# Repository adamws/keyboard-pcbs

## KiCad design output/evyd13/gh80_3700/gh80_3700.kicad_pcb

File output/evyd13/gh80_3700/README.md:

## evyd13/gh80_3700

[layout](gh80_3700-kle.json) - [PCB](gh80_3700.kicad_pcb)

{:loading="lazy"}

[Open in keyboard-layout-editor](http://www.keyboard-layout-editor.com/##@@_c=#aaaaaa;&=0,0&=0,1&=0,2&=0,3;&@_y:1&c=#777777;&=1,0&_c=#aaaaaa;&=1,1&=1,2&=1,3;&@_c=#cccccc;&=2,0&=2,1&=2,2&_c=#aaaaaa&h:2;&=3,3%0A%0A%0A1,0;&@_c=#cccccc;&=3,0&=3,1&=3,2;&@=4,0&=4,1&=4,2&_c=#777777&h:2;&=5,3%0A%0A%0A2,0;&@_c=#cccccc&w:2;&=5,0%0A%0A%0A0,0&=5,2;&@_x:4.25&y:-4&c=#aaaaaa;&=2,3%0A%0A%0A1,1;&@_x:4.25;&=3,3%0A%0A%0A1,1;&@_x:4.25;&=4,3%0A%0A%0A2,1;&@_x:4.25&c=#777777;&=5,3%0A%0A%0A2,1;&@_y:0.25&c=#cccccc;&=5,0%0A%0A%0A0,1&=5,1%0A%0A%0A0,1)

{:loading="lazy"}

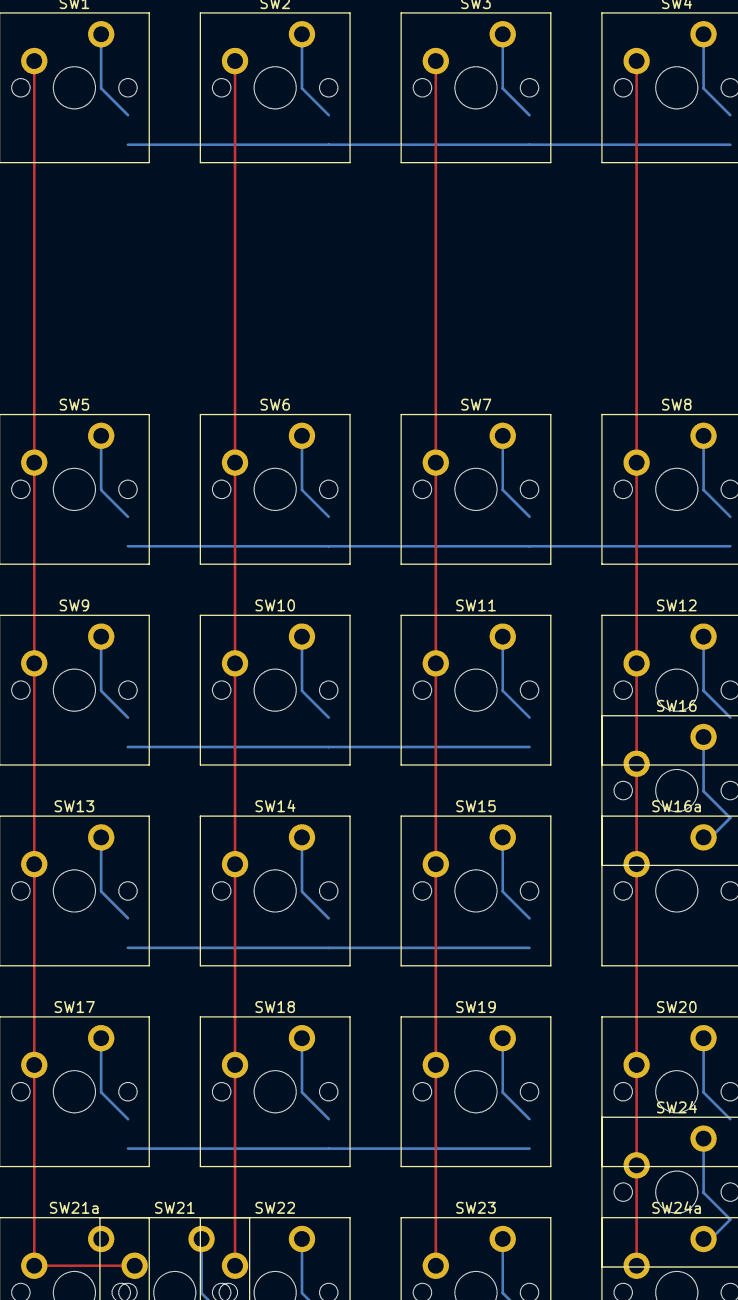
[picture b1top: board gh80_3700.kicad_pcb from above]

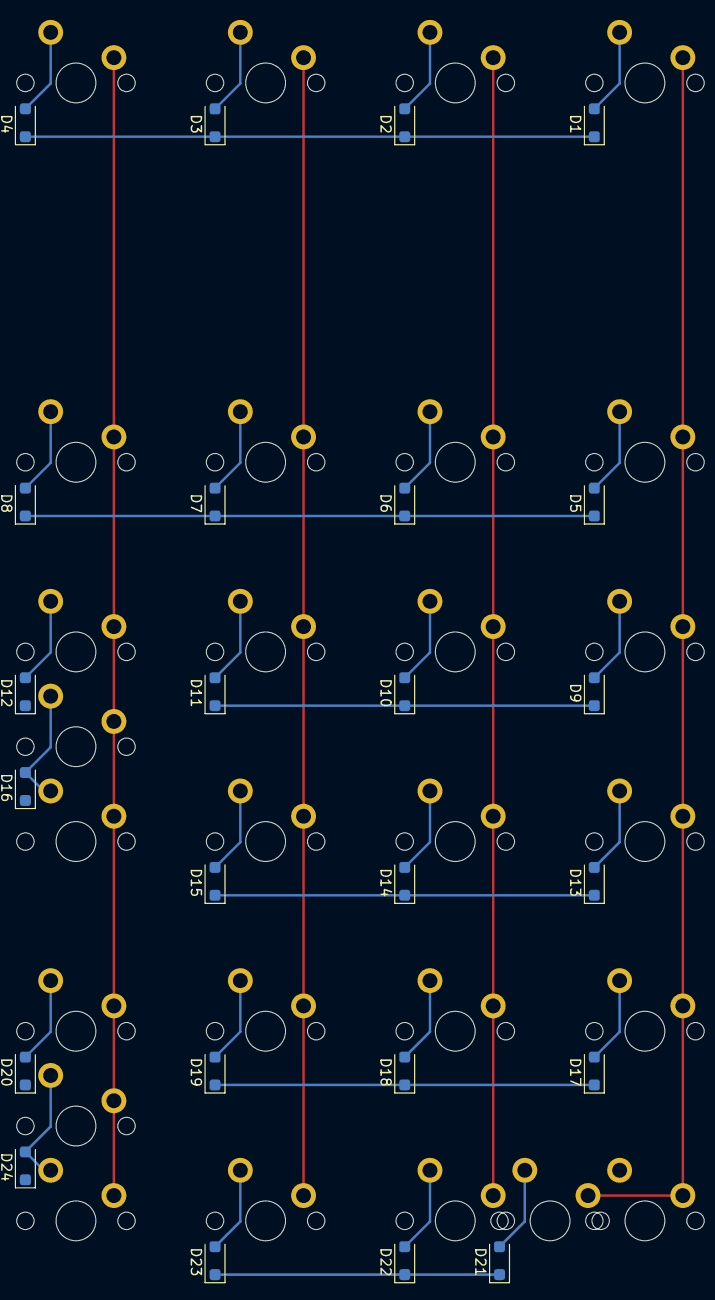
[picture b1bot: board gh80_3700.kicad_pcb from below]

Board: 2 copper layers, 51 parts (24 on the bottom side), 34 nets.

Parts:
D1, D2, D3, D4, D5, D6, D7, D8, D9, D10, D11, D12, D13, D14, D15, D16, D17, D18, D19, D20, D21, D22, D23, D24: D_SOD-123F
SW1, SW2, SW3, SW4, SW5, SW6, SW7, SW8, SW9, SW10, SW11, SW12, SW13, SW14, SW15, SW16, SW16a, SW17, SW18, SW19, SW20, SW21, SW21a, SW22, SW23, SW24, SW24a: SW_Cherry_MX_PCB_1.00u

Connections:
COL0: SW1.1, SW5.1, SW9.1, SW13.1, SW17.1, SW21.1, SW21a.1
COL1: SW2.1, SW6.1, SW10.1, SW14.1, SW18.1, SW22.1
COL2: SW3.1, SW7.1, SW11.1, SW15.1, SW19.1, SW23.1
COL3: SW4.1, SW8.1, SW12.1, SW16.1, SW16a.1, SW20.1, SW24.1, SW24a.1
unnamed: D1.2, SW1.2
unnamed: D2.2, SW2.2
unnamed: D3.2, SW3.2
unnamed: D4.2, SW4.2
unnamed: D5.2, SW5.2
unnamed: D6.2, SW6.2
unnamed: D7.2, SW7.2
unnamed: D8.2, SW8.2
unnamed: D9.2, SW9.2
unnamed: D10.2, SW10.2
unnamed: D11.2, SW11.2
unnamed: D12.2, SW12.2
unnamed: D13.2, SW13.2
unnamed: D14.2, SW14.2
unnamed: D15.2, SW15.2
unnamed: D16.2, SW16.2, SW16a.2
unnamed: D17.2, SW17.2
unnamed: D18.2, SW18.2
unnamed: D19.2, SW19.2
unnamed: D20.2, SW20.2
unnamed: D21.2, SW21.2, SW21a.2
unnamed: D22.2, SW22.2
unnamed: D23.2, SW23.2
unnamed: D24.2, SW24.2, SW24a.2
ROW0: D1.1, D2.1, D3.1, D4.1
ROW1: D5.1, D6.1, D7.1, D8.1
ROW2: D9.1, D10.1, D11.1, D12.1
ROW3: D13.1, D14.1, D15.1, D16.1
ROW4: D17.1, D18.1, D19.1, D20.1
ROW5: D21.1, D22.1, D23.1, D24.1

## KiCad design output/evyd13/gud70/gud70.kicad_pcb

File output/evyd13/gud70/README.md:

## evyd13/gud70

[layout](gud70-kle.json) - [PCB](gud70.kicad_pcb)

{:loading="lazy"}

[Open in keyboard-layout-editor](http://www.keyboard-layout-editor.com/##@@_c=#777777;&=0,0&_c=#cccccc;&=0,1&=0,2&=0,3&=0,4&=0,5&=0,6&=0,7&=0,8&=0,9&=0,10&=0,11&=0,12&_c=#aaaaaa&w:2;&=0,13%0A%0A%0A2,0&=0,14&=0,15;&@_w:1.5;&=1,0&_c=#cccccc;&=1,1&=1,2&=1,3&=1,4&=1,5&=1,6&=1,7&=1,8&=1,9&=1,10&=1,11&=1,12&_c=#aaaaaa&w:1.5;&=2,12%0A%0A%0A0,0&=1,14&=1,15;&@_w:1.75;&=2,0&_c=#cccccc;&=2,1&=2,2&=2,3&=2,4&=2,5&=2,6&=2,7&=2,8&=2,9&=2,10&=2,11&_c=#777777&w:2.25;&=2,13%0A%0A%0A0,0&_c=#aaaaaa;&=2,14&=2,15;&@_w:2.25;&=3,0%0A%0A%0A1,0&_c=#cccccc;&=3,2&=3,3&=3,4&=3,5&=3,6&=3,7&=3,8&=3,9&=3,10&=3,11&_c=#aaaaaa&w:1.75;&=3,12%0A%0A%0A3,0&=3,13%0A%0A%0A3,0&_c=#777777;&=3,14&_c=#aaaaaa;&=3,15;&@_w:1.5;&=4,0&=4,1&_w:1.5;&=4,2&_c=#cccccc&w:6;&=4,7&_c=#aaaaaa&w:1.5;&=4,10&=4,11%0A%0A%0A4,0&_w:1.5;&=4,12%0A%0A%0A4,0&_c=#777777;&=4,13&=4,14&=4,15;&@_y:0.25&c=#aaaaaa&w:1.25;&=3,0%0A%0A%0A1,1&=3,1%0A%0A%0A1,1&_x:9.25&w:1.5;&=4,11%0A%0A%0A4,1&=4,12%0A%0A%0A4,1;&@_x:12.25&y:0.25&w:2.75;&=3,12%0A%0A%0A3,1;&@_x:13&y:0.25&c=#777777;&=1,13%0A%0A%0A2,1&=0,13%0A%0A%0A2,1;&@_x:13.75&y:0.25&w:1.25&h:2&w2:1.5&h2:1&x2:-0.25;&=2,13%0A%0A%0A0,1;&@_x:12.75&c=#cccccc;&=2,12%0A%0A%0A0,1)

{:loading="lazy"}

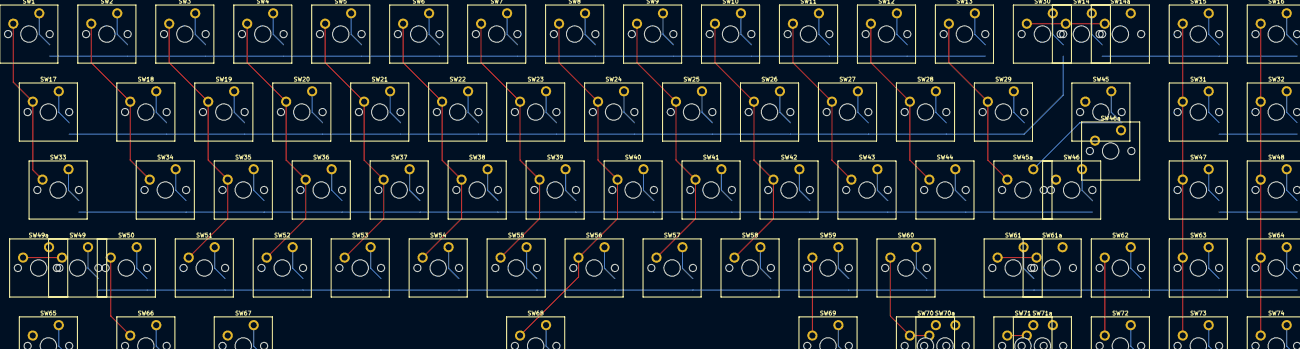
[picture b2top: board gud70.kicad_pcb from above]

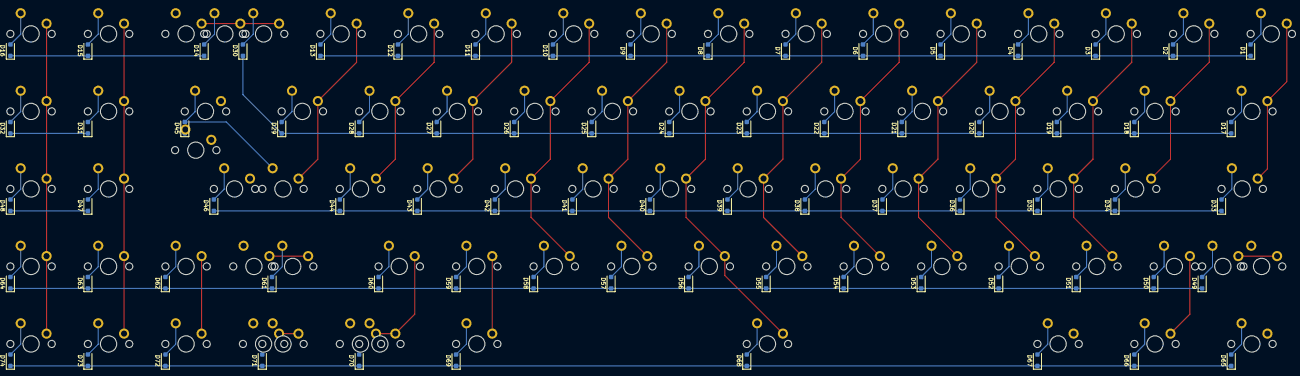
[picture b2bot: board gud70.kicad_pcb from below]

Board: 2 copper layers, 155 parts (74 on the bottom side), 95 nets.

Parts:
D1, D2, D3, D4, D5, D6, D7, D8, D9, D10, D11, D12, D13, D14, D15, D16, D17, D18, D19, D20, D21, D22, D23, D24, D25, D26, D27, D28, D29, D30, D31, D32, D33, D34, D35, D36, D37, D38, D39, D40, D41, D42, D43, D44, D45, D46, D47, D48, D49, D50, D51, D52, D53, D54, D55, D56, D57, D58, D59, D60, D61, D62, D63, D64, D65, D66, D67, D68, D69, D70, D71, D72, D73, D74: D_SOD-123F
SW1, SW2, SW3, SW4, SW5, SW6, SW7, SW8, SW9, SW10, SW11, SW12, SW13, SW14, SW14a, SW15, SW16, SW17, SW18, SW19, SW20, SW21, SW22, SW23, SW24, SW25, SW26, SW27, SW28, SW29, SW30, SW31, SW32, SW33, SW34, SW35, SW36, SW37, SW38, SW39, SW40, SW41, SW42, SW43, SW44, SW45, SW45a, SW46, SW46a, SW47, SW48, SW49, SW49a, SW50, SW51, SW52, SW53, SW54, SW55, SW56, SW57, SW58, SW59, SW60, SW61, SW61a, SW62, SW63, SW64, SW65, SW66, SW67, SW68, SW69, SW70, SW70a, SW71, SW71a, SW72, SW73, SW74: SW_Cherry_MX_PCB_1.00u

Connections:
COL0: SW1.1, SW17.1, SW33.1, SW49.1, SW49a.1, SW65.1
COL1: SW2.1, SW18.1, SW34.1, SW50.1, SW66.1
COL2: SW3.1, SW19.1, SW35.1, SW51.1, SW67.1
COL3: SW4.1, SW20.1, SW36.1, SW52.1
COL4: SW5.1, SW21.1, SW37.1, SW53.1
COL5: SW6.1, SW22.1, SW38.1, SW54.1
COL6: SW7.1, SW23.1, SW39.1, SW55.1
COL7: SW8.1, SW24.1, SW40.1, SW56.1, SW68.1
COL8: SW9.1, SW25.1, SW41.1, SW57.1
COL9: SW10.1, SW26.1, SW42.1, SW58.1
COL10: SW11.1, SW27.1, SW43.1, SW59.1, SW69.1
COL11: SW12.1, SW28.1, SW44.1, SW60.1, SW70.1, SW70a.1
COL12: SW13.1, SW29.1, SW45.1, SW45a.1, SW61.1, SW61a.1, SW71.1, SW71a.1
COL13: SW14.1, SW14a.1, SW30.1, SW46.1, SW46a.1, SW62.1, SW72.1
COL14: SW15.1, SW31.1, SW47.1, SW63.1, SW73.1
COL15: SW16.1, SW32.1, SW48.1, SW64.1, SW74.1
unnamed: D1.2, SW1.2
unnamed: D2.2, SW2.2
unnamed: D3.2, SW3.2
unnamed: D4.2, SW4.2
unnamed: D5.2, SW5.2
unnamed: D6.2, SW6.2
unnamed: D7.2, SW7.2
unnamed: D8.2, SW8.2
unnamed: D9.2, SW9.2
unnamed: D10.2, SW10.2
unnamed: D11.2, SW11.2
unnamed: D12.2, SW12.2
unnamed: D13.2, SW13.2
unnamed: D14.2, SW14.2, SW14a.2
unnamed: D15.2, SW15.2
unnamed: D16.2, SW16.2
unnamed: D17.2, SW17.2
unnamed: D18.2, SW18.2
unnamed: D19.2, SW19.2
unnamed: D20.2, SW20.2
unnamed: D21.2, SW21.2
unnamed: D22.2, SW22.2
unnamed: D23.2, SW23.2
unnamed: D24.2, SW24.2
unnamed: D25.2, SW25.2
unnamed: D26.2, SW26.2
unnamed: D27.2, SW27.2
unnamed: D28.2, SW28.2
unnamed: D29.2, SW29.2
unnamed: D30.2, SW30.2
unnamed: D31.2, SW31.2
unnamed: D32.2, SW32.2
unnamed: D33.2, SW33.2
unnamed: D34.2, SW34.2
unnamed: D35.2, SW35.2
unnamed: D36.2, SW36.2
unnamed: D37.2, SW37.2
unnamed: D38.2, SW38.2
unnamed: D39.2, SW39.2
unnamed: D40.2, SW40.2
unnamed: D41.2, SW41.2
unnamed: D42.2, SW42.2
unnamed: D43.2, SW43.2
unnamed: D44.2, SW44.2
unnamed: D45.2, SW45.2, SW45a.2
unnamed: D46.2, SW46.2, SW46a.2
unnamed: D47.2, SW47.2
unnamed: D48.2, SW48.2
unnamed: D49.2, SW49.2, SW49a.2
unnamed: D50.2, SW50.2
unnamed: D51.2, SW51.2
unnamed: D52.2, SW52.2
unnamed: D53.2, SW53.2
unnamed: D54.2, SW54.2
unnamed: D55.2, SW55.2
unnamed: D56.2, SW56.2
unnamed: D57.2, SW57.2
unnamed: D58.2, SW58.2
unnamed: D59.2, SW59.2
unnamed: D60.2, SW60.2
unnamed: D61.2, SW61.2, SW61a.2
unnamed: D62.2, SW62.2
unnamed: D63.2, SW63.2
unnamed: D64.2, SW64.2
unnamed: D65.2, SW65.2
unnamed: D66.2, SW66.2
unnamed: D67.2, SW67.2
unnamed: D68.2, SW68.2
unnamed: D69.2, SW69.2
unnamed: D70.2, SW70.2, SW70a.2
unnamed: D71.2, SW71.2, SW71a.2
unnamed: D72.2, SW72.2
unnamed: D73.2, SW73.2
unnamed: D74.2, SW74.2
ROW0: D1.1, D2.1, D3.1, D4.1, D5.1, D6.1, D7.1, D8.1, D9.1, D10.1, D11.1, D12.1, D13.1, D14.1, D15.1, D16.1
ROW1: D17.1, D18.1, D19.1, D20.1, D21.1, D22.1, D23.1, D24.1, D25.1, D26.1, D27.1, D28.1, D29.1, D30.1, D31.1, D32.1
ROW2: D33.1, D34.1, D35.1, D36.1, D37.1, D38.1, D39.1, D40.1, D41.1, D42.1, D43.1, D44.1, D45.1, D46.1, D47.1, D48.1
ROW3: D49.1, D50.1, D51.1, D52.1, D53.1, D54.1, D55.1, D56.1, D57.1, D58.1, D59.1, D60.1, D61.1, D62.1, D63.1, D64.1
ROW4: D65.1, D66.1, D67.1, D68.1, D69.1, D70.1, D71.1, D72.1, D73.1, D74.1
